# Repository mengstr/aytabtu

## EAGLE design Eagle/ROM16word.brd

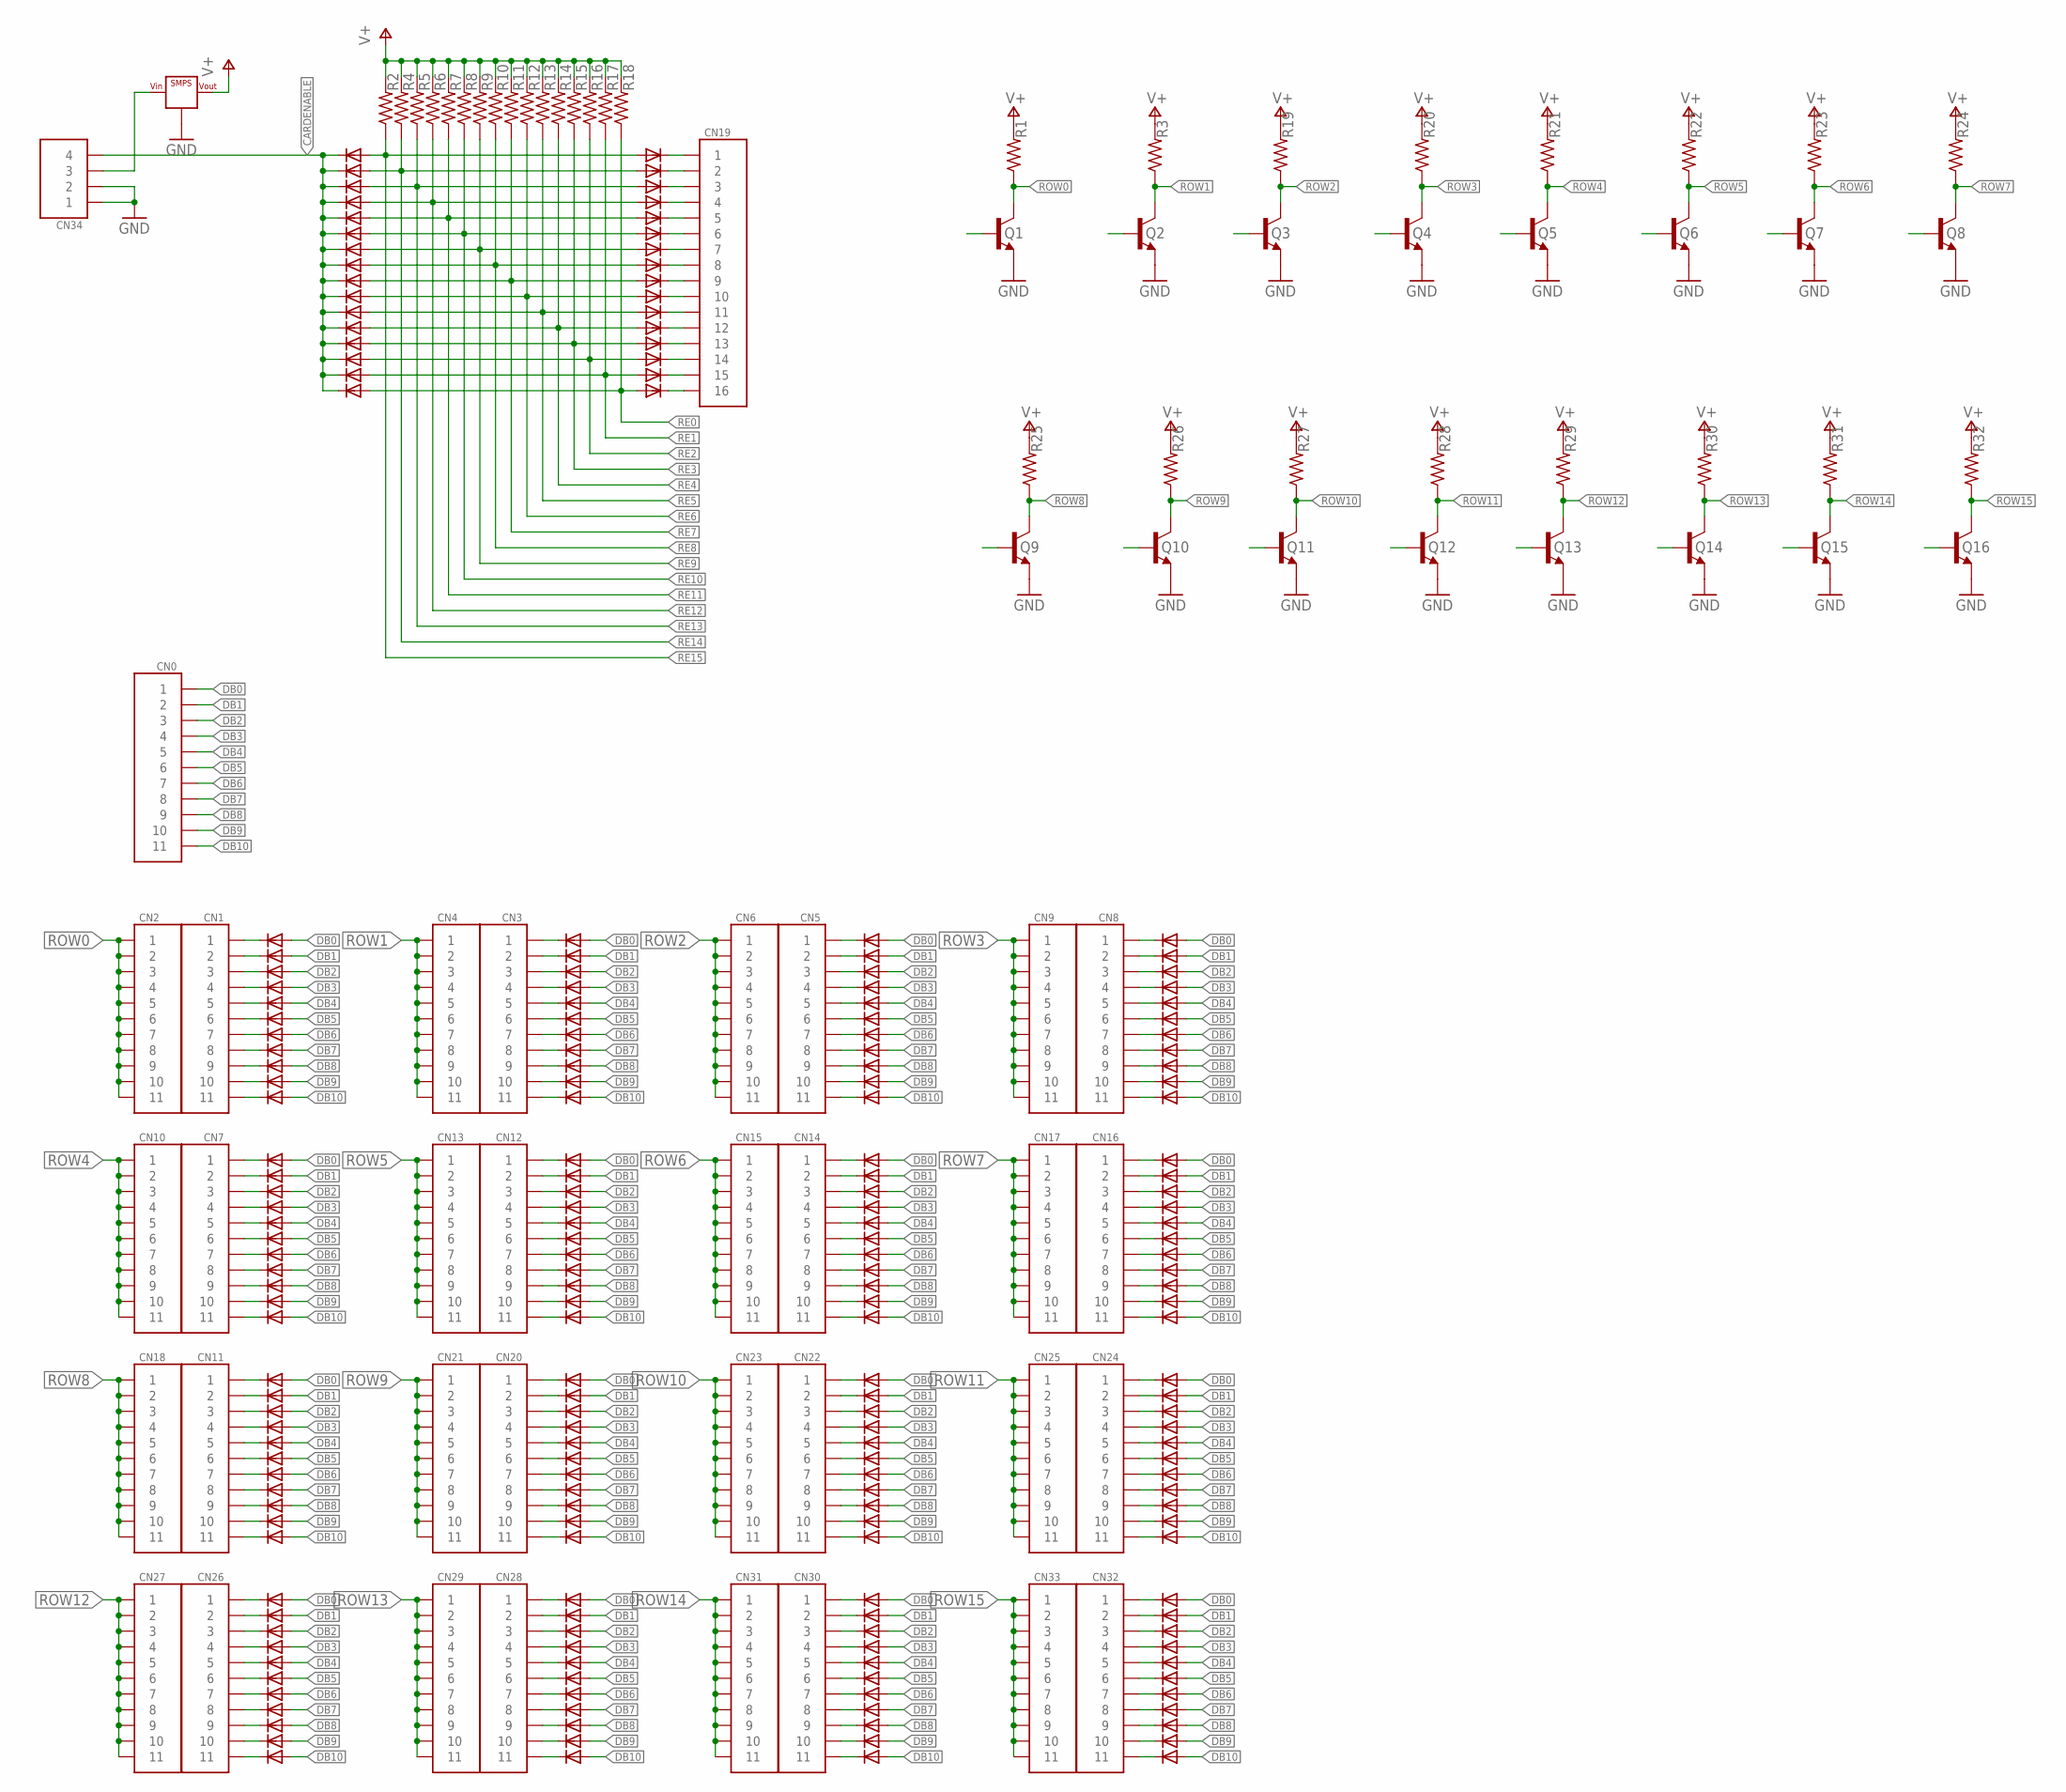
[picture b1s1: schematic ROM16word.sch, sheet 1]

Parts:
CN0, CN1, CN2, CN3, CN4, CN5, CN6, CN7, CN8, CN9, CN10, CN11, CN12, CN13, CN14, CN15, CN16, CN17, CN18, CN20, CN21, CN22, CN23, CN24, CN25, CN26, CN27, CN28, CN29, CN30, CN31, CN32, CN33: HD11
CN19: HD16
CN34: HD4
D1, D2, D3, D4, D5, D6, D7, D8, D9, D10, D11, D12, D13, D14, D15, D16, D17, D18, D19, D20, D21, D22, D23, D24, D25, D26, D27, D28, D29, D30, D31, D32, D33, D34, D35, D36, D37, D38, D39, D40, D41, D42, D43, D44, D45, D46, D47, D48, D49, D50, D51, D52, D53, D54, D55, D56, D57, D58, D59, D60, D61, D62, D63, D64, D65, D66, D67, D68, D69, D70, D71, D72, D73, D74, D75, D76, D77, D78, D79, D80, D81, D82, D83, D84, D85, D86, D87, D88, D89, D90, D91, D92, D93, D94, D95, D96, D97, D98, D99, D100, D101, D102, D103, D104, D105, D106, D107, D108, D109, D110, D111, D112, D113, D114, D115, D116, D117, D118, D119, D120, D121, D122, D123, D124, D125, D126, D127, D128, D129, D130, D131, D132, D133, D134, D135, D136, D137, D138, D139, D140, D141, D142, D143, D144, D145, D146, D147, D148, D149, D150, D151, D152, D153, D154, D155, D156, D157, D158, D159, D160, D161, D162, D163, D164, D165, D166, D167, D168, D169, D170, D171, D172, D173, D174, D175, D176: DIODE-6.3; DO35-6.3
D177, D178, D179, D180, D181, D182, D183, D184, D185, D186, D187, D188, D189, D190, D191, D192, D193, D194, D195, D196, D197, D198, D199, D200, D201, D202, D203, D204, D205, D206, D207, D208: DIODE-5.08; DO35-5.08
Q1, Q2, Q3, Q4, Q5, Q6, Q7, Q8, Q9, Q10, Q11, Q12, Q13, Q14, Q15, Q16: BC547-STRAIGHT; TO92-S-CBE
R1, R2, R3, R4, R5, R6, R7, R8, R9, R10, R11, R12, R13, R14, R15, R16, R17, R18, R19, R20, R21, R22, R23, R24, R25, R26, R27, R28, R29, R30, R31, R32: R1/8-6MM; R0125-6.3
VR1: SMPS; BUCK1722

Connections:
CARDENABLE: CN34.P$4 (4), D182.C, D183.C, D184.C, D185.C, D186.C, D187.C, D188.C, D189.C, D190.C, D191.C, D192.C, D193.C, D194.C, D195.C, D196.C, D197.C
DB0: CN0.P$1 (1), D1.A, D12.A, D23.A, D34.A, D45.A, D56.A, D67.A, D78.A, D89.A, D100.A, D111.A, D122.A, D133.A, D144.A, D155.A, D166.A
DB1: CN0.P$2 (2), D2.A, D13.A, D24.A, D35.A, D46.A, D57.A, D68.A, D79.A, D90.A, D101.A, D112.A, D123.A, D134.A, D145.A, D156.A, D167.A
DB2: CN0.P$3 (3), D3.A, D14.A, D25.A, D36.A, D47.A, D58.A, D69.A, D80.A, D91.A, D102.A, D113.A, D124.A, D135.A, D146.A, D157.A, D168.A
DB3: CN0.P$4 (4), D4.A, D15.A, D26.A, D37.A, D48.A, D59.A, D70.A, D81.A, D92.A, D103.A, D114.A, D125.A, D136.A, D147.A, D158.A, D169.A
DB4: CN0.P$5 (5), D5.A, D16.A, D27.A, D38.A, D49.A, D60.A, D71.A, D82.A, D93.A, D104.A, D115.A, D126.A, D137.A, D148.A, D159.A, D170.A
DB5: CN0.P$6 (6), D6.A, D17.A, D28.A, D39.A, D50.A, D61.A, D72.A, D83.A, D94.A, D105.A, D116.A, D127.A, D138.A, D149.A, D160.A, D171.A
DB6: CN0.P$7 (7), D7.A, D18.A, D29.A, D40.A, D51.A, D62.A, D73.A, D84.A, D95.A, D106.A, D117.A, D128.A, D139.A, D150.A, D161.A, D172.A
DB7: CN0.P$8 (8), D8.A, D19.A, D30.A, D41.A, D52.A, D63.A, D74.A, D85.A, D96.A, D107.A, D118.A, D129.A, D140.A, D151.A, D162.A, D173.A
DB8: CN0.P$9 (9), D9.A, D20.A, D31.A, D42.A, D53.A, D64.A, D75.A, D86.A, D97.A, D108.A, D119.A, D130.A, D141.A, D152.A, D163.A, D174.A
DB9: CN0.P$10 (10), D10.A, D21.A, D32.A, D43.A, D54.A, D65.A, D76.A, D87.A, D98.A, D109.A, D120.A, D131.A, D142.A, D153.A, D164.A, D175.A
DB10: CN0.P$11 (11), D11.A, D22.A, D33.A, D44.A, D55.A, D66.A, D77.A, D88.A, D99.A, D110.A, D121.A, D132.A, D143.A, D154.A, D165.A, D176.A
GND: CN34.P$1 (1), CN34.P$2 (2), Q1.E, Q2.E, Q3.E, Q4.E, Q5.E, Q6.E, Q7.E, Q8.E, Q9.E, Q10.E, Q11.E, Q12.E, Q13.E, Q14.E, Q15.E, Q16.E, VR1.GND@1 (GND), VR1.GND@2 (GND), VR1.GND@3 (GND), VR1.GND@4 (GND)
unnamed: CN1.P$1 (1), D1.C
unnamed: CN1.P$2 (2), D2.C
unnamed: CN1.P$3 (3), D3.C
unnamed: CN1.P$4 (4), D4.C
unnamed: CN1.P$5 (5), D5.C
unnamed: CN1.P$6 (6), D6.C
unnamed: CN1.P$7 (7), D7.C
unnamed: CN1.P$8 (8), D8.C
unnamed: CN1.P$9 (9), D9.C
unnamed: CN1.P$10 (10), D10.C
unnamed: CN1.P$11 (11), D11.C
unnamed: CN3.P$1 (1), D12.C
unnamed: CN3.P$2 (2), D13.C
unnamed: CN3.P$3 (3), D14.C
unnamed: CN3.P$4 (4), D15.C
unnamed: CN3.P$5 (5), D16.C
unnamed: CN3.P$6 (6), D17.C
unnamed: CN3.P$7 (7), D18.C
unnamed: CN3.P$8 (8), D19.C
unnamed: CN3.P$9 (9), D20.C
unnamed: CN3.P$10 (10), D21.C
unnamed: CN3.P$11 (11), D22.C
unnamed: CN5.P$1 (1), D23.C
unnamed: CN5.P$2 (2), D24.C
unnamed: CN5.P$3 (3), D25.C
unnamed: CN5.P$4 (4), D26.C
unnamed: CN5.P$5 (5), D27.C
unnamed: CN5.P$6 (6), D28.C
unnamed: CN5.P$7 (7), D29.C
unnamed: CN5.P$8 (8), D30.C
unnamed: CN5.P$9 (9), D31.C
unnamed: CN5.P$10 (10), D32.C
unnamed: CN5.P$11 (11), D33.C
unnamed: CN8.P$1 (1), D34.C
unnamed: CN8.P$2 (2), D35.C
unnamed: CN8.P$3 (3), D36.C
unnamed: CN8.P$4 (4), D37.C
unnamed: CN8.P$5 (5), D38.C
unnamed: CN8.P$6 (6), D39.C
unnamed: CN8.P$7 (7), D40.C
unnamed: CN8.P$8 (8), D41.C
unnamed: CN8.P$9 (9), D42.C
unnamed: CN8.P$10 (10), D43.C
unnamed: CN8.P$11 (11), D44.C
unnamed: CN7.P$1 (1), D45.C
unnamed: CN7.P$2 (2), D46.C
unnamed: CN7.P$3 (3), D47.C
unnamed: CN7.P$4 (4), D48.C
unnamed: CN7.P$5 (5), D49.C
unnamed: CN7.P$6 (6), D50.C
unnamed: CN7.P$7 (7), D51.C
unnamed: CN7.P$8 (8), D52.C
unnamed: CN7.P$9 (9), D53.C
unnamed: CN7.P$10 (10), D54.C
unnamed: CN7.P$11 (11), D55.C
unnamed: CN12.P$1 (1), D56.C
unnamed: CN12.P$2 (2), D57.C
unnamed: CN12.P$3 (3), D58.C
unnamed: CN12.P$4 (4), D59.C
unnamed: CN12.P$5 (5), D60.C
unnamed: CN12.P$6 (6), D61.C
unnamed: CN12.P$7 (7), D62.C
unnamed: CN12.P$8 (8), D63.C
unnamed: CN12.P$9 (9), D64.C
unnamed: CN12.P$10 (10), D65.C
unnamed: CN12.P$11 (11), D66.C
unnamed: CN14.P$1 (1), D67.C
unnamed: CN14.P$2 (2), D68.C
unnamed: CN14.P$3 (3), D69.C
unnamed: CN14.P$4 (4), D70.C
unnamed: CN14.P$5 (5), D71.C
unnamed: CN14.P$6 (6), D72.C
unnamed: CN14.P$7 (7), D73.C
unnamed: CN14.P$8 (8), D74.C
unnamed: CN14.P$9 (9), D75.C
unnamed: CN14.P$10 (10), D76.C
unnamed: CN14.P$11 (11), D77.C
unnamed: CN16.P$1 (1), D78.C
unnamed: CN16.P$2 (2), D79.C
unnamed: CN16.P$3 (3), D80.C
unnamed: CN16.P$4 (4), D81.C
unnamed: CN16.P$5 (5), D82.C
unnamed: CN16.P$6 (6), D83.C
unnamed: CN16.P$7 (7), D84.C
unnamed: CN16.P$8 (8), D85.C
unnamed: CN16.P$9 (9), D86.C
unnamed: CN16.P$10 (10), D87.C
unnamed: CN16.P$11 (11), D88.C
unnamed: CN11.P$1 (1), D89.C
unnamed: CN11.P$2 (2), D90.C
unnamed: CN11.P$3 (3), D91.C
unnamed: CN11.P$4 (4), D92.C
unnamed: CN11.P$5 (5), D93.C
unnamed: CN11.P$6 (6), D94.C
unnamed: CN11.P$7 (7), D95.C
unnamed: CN11.P$8 (8), D96.C
unnamed: CN11.P$9 (9), D97.C
unnamed: CN11.P$10 (10), D98.C
unnamed: CN11.P$11 (11), D99.C
unnamed: CN20.P$1 (1), D100.C
unnamed: CN20.P$2 (2), D101.C
unnamed: CN20.P$3 (3), D102.C
unnamed: CN20.P$4 (4), D103.C
unnamed: CN20.P$5 (5), D104.C
unnamed: CN20.P$6 (6), D105.C
unnamed: CN20.P$7 (7), D106.C
unnamed: CN20.P$8 (8), D107.C
unnamed: CN20.P$9 (9), D108.C
unnamed: CN20.P$10 (10), D109.C
unnamed: CN20.P$11 (11), D110.C
unnamed: CN22.P$1 (1), D111.C
unnamed: CN22.P$2 (2), D112.C
unnamed: CN22.P$3 (3), D113.C
unnamed: CN22.P$4 (4), D114.C
unnamed: CN22.P$5 (5), D115.C
unnamed: CN22.P$6 (6), D116.C
unnamed: CN22.P$7 (7), D117.C
unnamed: CN22.P$8 (8), D118.C
unnamed: CN22.P$9 (9), D119.C
unnamed: CN22.P$10 (10), D120.C
unnamed: CN22.P$11 (11), D121.C
unnamed: CN24.P$1 (1), D122.C
unnamed: CN24.P$2 (2), D123.C
unnamed: CN24.P$3 (3), D124.C
unnamed: CN24.P$4 (4), D125.C
unnamed: CN24.P$5 (5), D126.C
unnamed: CN24.P$6 (6), D127.C
unnamed: CN24.P$7 (7), D128.C
unnamed: CN24.P$8 (8), D129.C
unnamed: CN24.P$9 (9), D130.C
unnamed: CN24.P$10 (10), D131.C
unnamed: CN24.P$11 (11), D132.C
unnamed: CN26.P$1 (1), D133.C
unnamed: CN26.P$2 (2), D134.C
unnamed: CN26.P$3 (3), D135.C
unnamed: CN26.P$4 (4), D136.C
unnamed: CN26.P$5 (5), D137.C
unnamed: CN26.P$6 (6), D138.C
unnamed: CN26.P$7 (7), D139.C
unnamed: CN26.P$8 (8), D140.C
unnamed: CN26.P$9 (9), D141.C
unnamed: CN26.P$10 (10), D142.C
unnamed: CN26.P$11 (11), D143.C
unnamed: CN28.P$1 (1), D144.C
unnamed: CN28.P$2 (2), D145.C
unnamed: CN28.P$3 (3), D146.C
unnamed: CN28.P$4 (4), D147.C
unnamed: CN28.P$5 (5), D148.C
unnamed: CN28.P$6 (6), D149.C
unnamed: CN28.P$7 (7), D150.C
unnamed: CN28.P$8 (8), D151.C
unnamed: CN28.P$9 (9), D152.C
unnamed: CN28.P$10 (10), D153.C
unnamed: CN28.P$11 (11), D154.C
unnamed: CN30.P$1 (1), D155.C
unnamed: CN30.P$2 (2), D156.C
unnamed: CN30.P$3 (3), D157.C
unnamed: CN30.P$4 (4), D158.C
unnamed: CN30.P$5 (5), D159.C
unnamed: CN30.P$6 (6), D160.C
unnamed: CN30.P$7 (7), D161.C
unnamed: CN30.P$8 (8), D162.C
unnamed: CN30.P$9 (9), D163.C
unnamed: CN30.P$10 (10), D164.C
unnamed: CN30.P$11 (11), D165.C
unnamed: CN32.P$1 (1), D166.C
unnamed: CN32.P$2 (2), D167.C
unnamed: CN32.P$3 (3), D168.C
unnamed: CN32.P$4 (4), D169.C
unnamed: CN32.P$5 (5), D170.C
unnamed: CN32.P$6 (6), D171.C
unnamed: CN32.P$7 (7), D172.C
unnamed: CN32.P$8 (8), D173.C
unnamed: CN32.P$9 (9), D174.C
unnamed: CN32.P$10 (10), D175.C
unnamed: CN32.P$11 (11), D176.C
POW: CN34.P$3 (3), VR1.IN@1 (VIN), VR1.IN@2 (VIN)
RE0: D197.A, D208.A, R18.1
RE1: D196.A, D207.A, R17.1
RE2: D195.A, D206.A, R16.1
RE3: D194.A, D205.A, R15.1
RE4: D193.A, D204.A, R14.1
RE5: D192.A, D203.A, R13.1
RE6: D191.A, D202.A, R12.1
RE7: D190.A, D201.A, R11.1
RE8: D189.A, D200.A, R10.1
RE9: D188.A, D199.A, R9.1
RE10: D187.A, D198.A, R8.1
RE11: D181.A, D186.A, R7.1
RE12: D180.A, D185.A, R6.1
RE13: D179.A, D184.A, R5.1
RE14: D178.A, D183.A, R4.1
RE15: D177.A, D182.A, R2.1
ROW0: CN2.P$1 (1), CN2.P$2 (2), CN2.P$3 (3), CN2.P$4 (4), CN2.P$5 (5), CN2.P$6 (6), CN2.P$7 (7), CN2.P$8 (8), CN2.P$9 (9), CN2.P$10 (10), CN2.P$11 (11), Q1.C, R1.1
ROW1: CN4.P$1 (1), CN4.P$2 (2), CN4.P$3 (3), CN4.P$4 (4), CN4.P$5 (5), CN4.P$6 (6), CN4.P$7 (7), CN4.P$8 (8), CN4.P$9 (9), CN4.P$10 (10), CN4.P$11 (11), Q2.C, R3.1
ROW2: CN6.P$1 (1), CN6.P$2 (2), CN6.P$3 (3), CN6.P$4 (4), CN6.P$5 (5), CN6.P$6 (6), CN6.P$7 (7), CN6.P$8 (8), CN6.P$9 (9), CN6.P$10 (10), CN6.P$11 (11), Q3.C, R19.1
ROW3: CN9.P$1 (1), CN9.P$2 (2), CN9.P$3 (3), CN9.P$4 (4), CN9.P$5 (5), CN9.P$6 (6), CN9.P$7 (7), CN9.P$8 (8), CN9.P$9 (9), CN9.P$10 (10), CN9.P$11 (11), Q4.C, R20.1
ROW4: CN10.P$1 (1), CN10.P$2 (2), CN10.P$3 (3), CN10.P$4 (4), CN10.P$5 (5), CN10.P$6 (6), CN10.P$7 (7), CN10.P$8 (8), CN10.P$9 (9), CN10.P$10 (10), CN10.P$11 (11), Q5.C, R21.1
ROW5: CN13.P$1 (1), CN13.P$2 (2), CN13.P$3 (3), CN13.P$4 (4), CN13.P$5 (5), CN13.P$6 (6), CN13.P$7 (7), CN13.P$8 (8), CN13.P$9 (9), CN13.P$10 (10), CN13.P$11 (11), Q6.C, R22.1
ROW6: CN15.P$1 (1), CN15.P$2 (2), CN15.P$3 (3), CN15.P$4 (4), CN15.P$5 (5), CN15.P$6 (6), CN15.P$7 (7), CN15.P$8 (8), CN15.P$9 (9), CN15.P$10 (10), CN15.P$11 (11), Q7.C, R23.1
ROW7: CN17.P$1 (1), CN17.P$2 (2), CN17.P$3 (3), CN17.P$4 (4), CN17.P$5 (5), CN17.P$6 (6), CN17.P$7 (7), CN17.P$8 (8), CN17.P$9 (9), CN17.P$10 (10), CN17.P$11 (11), Q8.C, R24.1
ROW8: CN18.P$1 (1), CN18.P$2 (2), CN18.P$3 (3), CN18.P$4 (4), CN18.P$5 (5), CN18.P$6 (6), CN18.P$7 (7), CN18.P$8 (8), CN18.P$9 (9), CN18.P$10 (10), CN18.P$11 (11), Q9.C, R25.1
ROW9: CN21.P$1 (1), CN21.P$2 (2), CN21.P$3 (3), CN21.P$4 (4), CN21.P$5 (5), CN21.P$6 (6), CN21.P$7 (7), CN21.P$8 (8), CN21.P$9 (9), CN21.P$10 (10), CN21.P$11 (11), Q10.C, R26.1
ROW10: CN23.P$1 (1), CN23.P$2 (2), CN23.P$3 (3), CN23.P$4 (4), CN23.P$5 (5), CN23.P$6 (6), CN23.P$7 (7), CN23.P$8 (8), CN23.P$9 (9), CN23.P$10 (10), CN23.P$11 (11), Q11.C, R27.1
ROW11: CN25.P$1 (1), CN25.P$2 (2), CN25.P$3 (3), CN25.P$4 (4), CN25.P$5 (5), CN25.P$6 (6), CN25.P$7 (7), CN25.P$8 (8), CN25.P$9 (9), CN25.P$10 (10), CN25.P$11 (11), Q12.C, R28.1
ROW12: CN27.P$1 (1), CN27.P$2 (2), CN27.P$3 (3), CN27.P$4 (4), CN27.P$5 (5), CN27.P$6 (6), CN27.P$7 (7), CN27.P$8 (8), CN27.P$9 (9), CN27.P$10 (10), CN27.P$11 (11), Q13.C, R29.1
ROW13: CN29.P$1 (1), CN29.P$2 (2), CN29.P$3 (3), CN29.P$4 (4), CN29.P$5 (5), CN29.P$6 (6), CN29.P$7 (7), CN29.P$8 (8), CN29.P$9 (9), CN29.P$10 (10), CN29.P$11 (11), Q14.C, R30.1
ROW14: CN31.P$1 (1), CN31.P$2 (2), CN31.P$3 (3), CN31.P$4 (4), CN31.P$5 (5), CN31.P$6 (6), CN31.P$7 (7), CN31.P$8 (8), CN31.P$9 (9), CN31.P$10 (10), CN31.P$11 (11), Q15.C, R31.1
ROW15: CN33.P$1 (1), CN33.P$2 (2), CN33.P$3 (3), CN33.P$4 (4), CN33.P$5 (5), CN33.P$6 (6), CN33.P$7 (7), CN33.P$8 (8), CN33.P$9 (9), CN33.P$10 (10), CN33.P$11 (11), Q16.C, R32.1
SEL0: CN19.P$1 (1), D177.C
SEL1: CN19.P$2 (2), D178.C
SEL2: CN19.P$3 (3), D179.C
SEL3: CN19.P$4 (4), D180.C
SEL4: CN19.P$5 (5), D181.C
SEL5: CN19.P$6 (6), D198.C
SEL6: CN19.P$7 (7), D199.C
SEL7: CN19.P$8 (8), D200.C
SEL8: CN19.P$9 (9), D201.C
SEL9: CN19.P$10 (10), D202.C
SEL10: CN19.P$11 (11), D203.C
SEL11: CN19.P$12 (12), D204.C
SEL12: CN19.P$13 (13), D205.C
SEL13: CN19.P$14 (14), D206.C
SEL14: CN19.P$15 (15), D207.C
SEL15: CN19.P$16 (16), D208.C
V+: R1.2, R2.2, R3.2, R4.2, R5.2, R6.2, R7.2, R8.2, R9.2, R10.2, R11.2, R12.2, R13.2, R14.2, R15.2, R16.2, R17.2, R18.2, R19.2, R20.2, R21.2, R22.2, R23.2, R24.2, R25.2, R26.2, R27.2, R28.2, R29.2, R30.2, R31.2, R32.2, VR1.OUT@1 (VOUT), VR1.OUT@2 (VOUT)

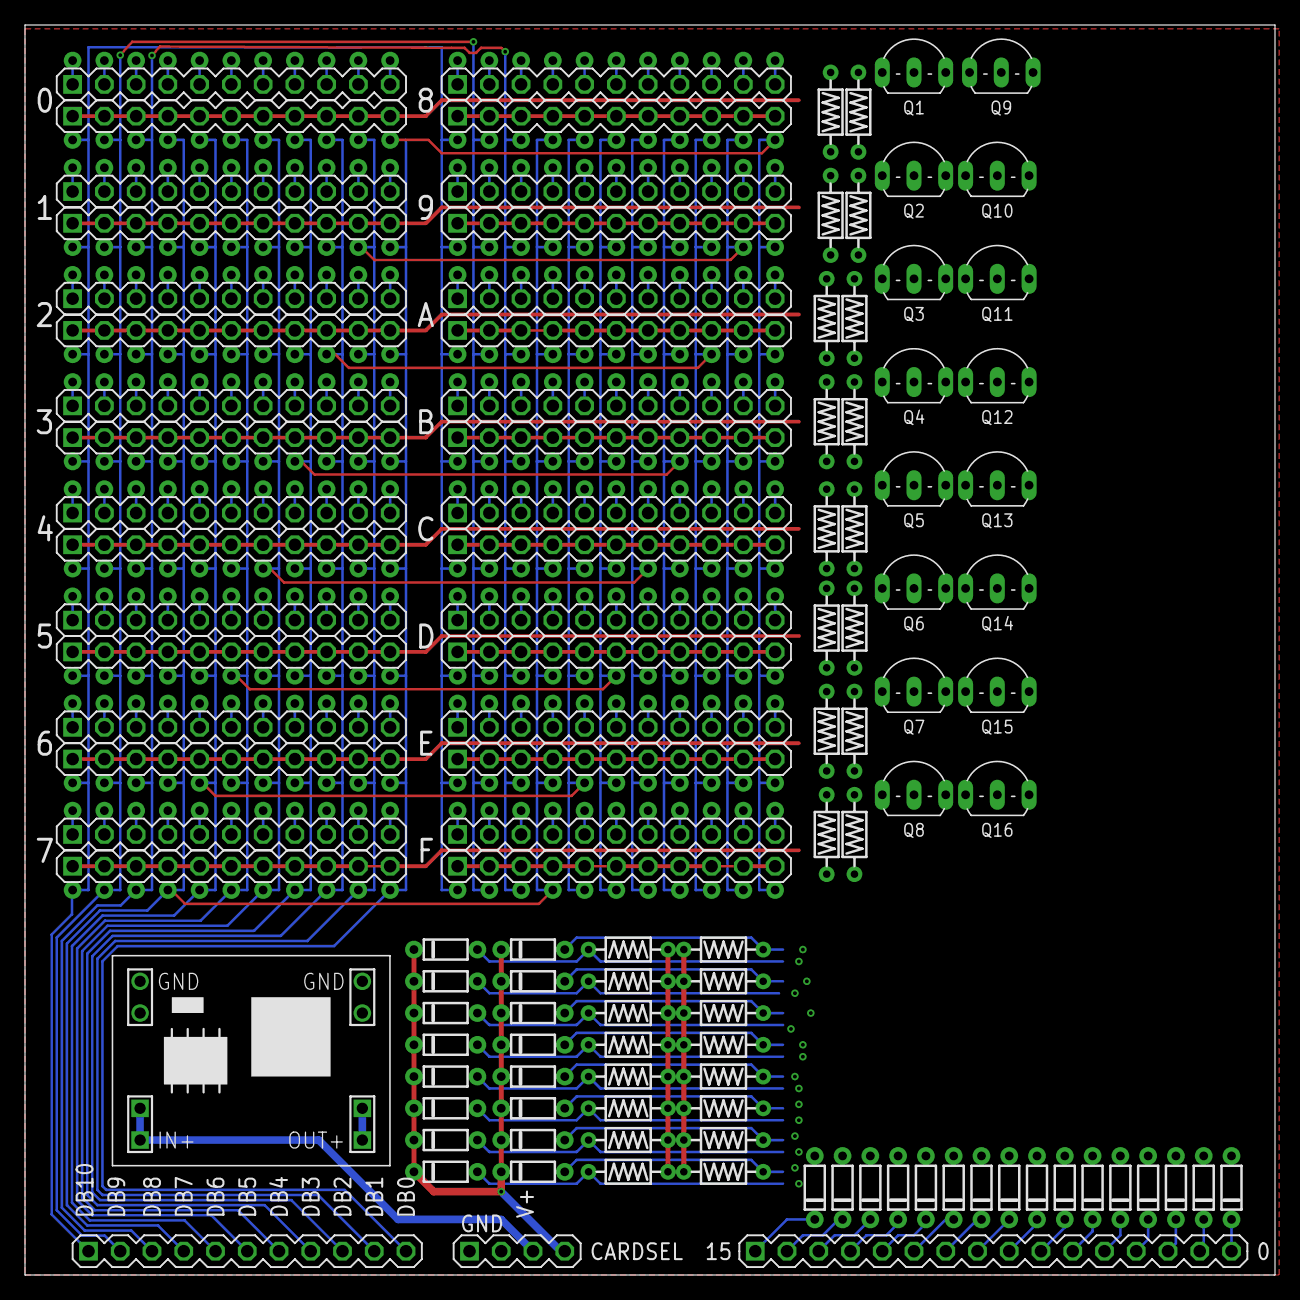
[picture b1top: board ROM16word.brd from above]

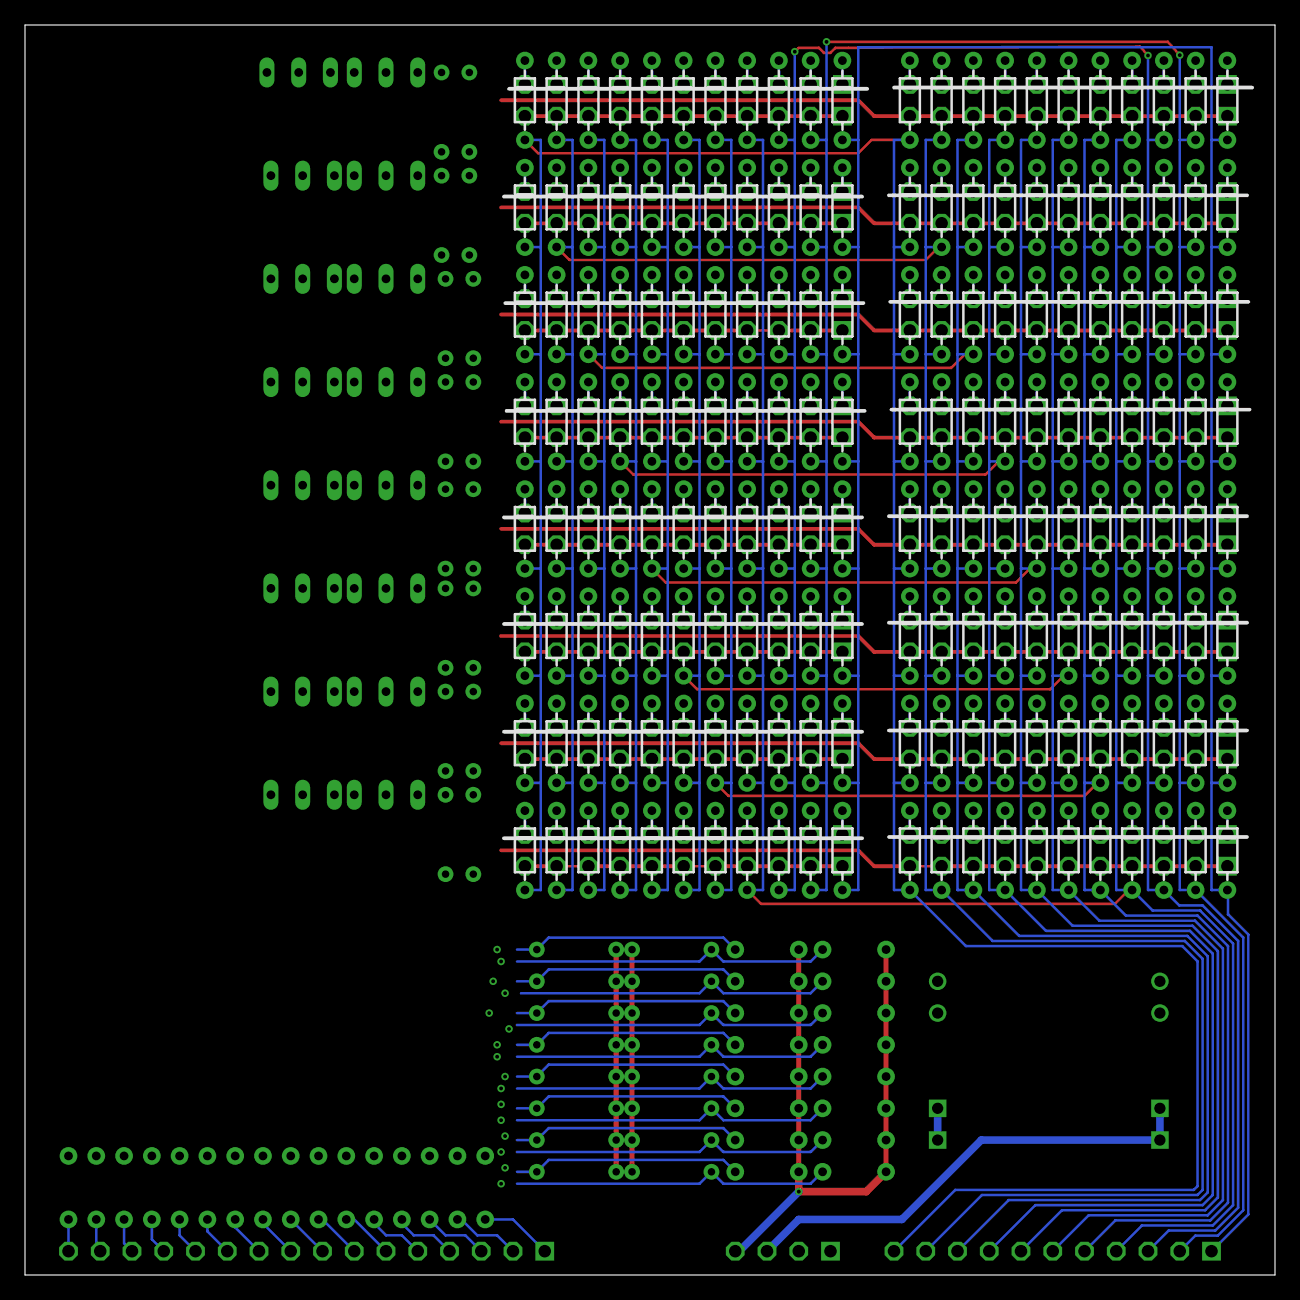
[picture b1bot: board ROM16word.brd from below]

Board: 2 copper layers, 100.0 x 100.0 mm, 292 parts (176 on the bottom side), 239 nets.

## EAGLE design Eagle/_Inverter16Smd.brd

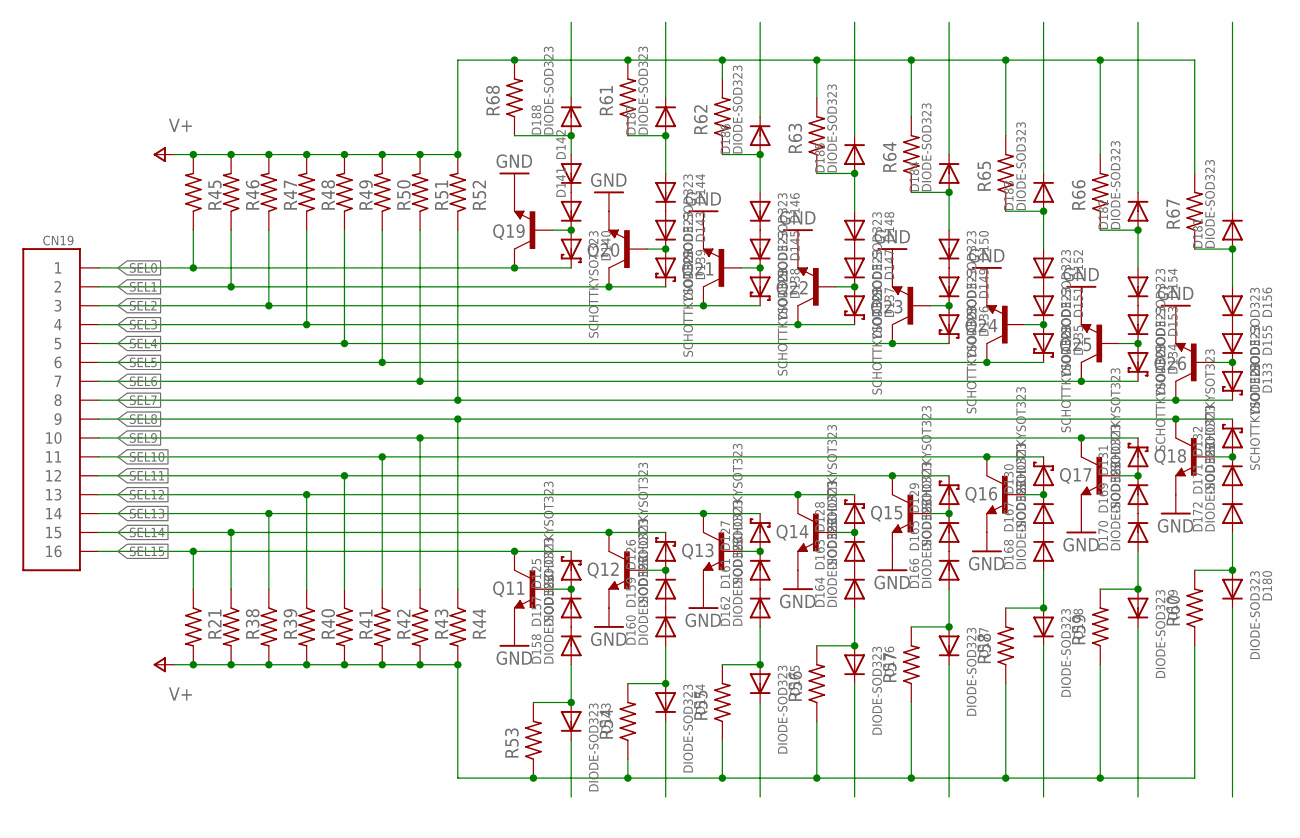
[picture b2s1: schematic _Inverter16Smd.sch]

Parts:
CN19: HD16
D125, D126, D127, D128, D129, D130, D131, D132, D133, D134, D135, D136, D137, D138, D139, D140: SCHOTTKYSOT323; SOT23
D141, D142, D143, D144, D145, D146, D147, D148, D149, D150, D151, D152, D153, D154, D155, D156, D157, D158, D159, D160, D161, D162, D163, D164, D165, D166, D167, D168, D169, D170, D171, D172, D173, D174, D175, D176, D177, D178, D179, D180, D181, D182, D183, D184, D185, D186, D187, D188: DIODE-SOD323; SOD323F
Q11, Q12, Q13, Q14, Q15, Q16, Q17, Q18, Q19, Q20, Q21, Q22, Q23, Q24, Q25, Q26: BC547-SOT23; SOT23
R21, R38, R39, R40, R41, R42, R43, R44, R45, R46, R47, R48, R49, R50, R51, R52, R53, R54, R55, R56, R57, R58, R59, R60, R61, R62, R63, R64, R65, R66, R67, R68: R-0805; R0805

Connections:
GND: Q11.2 (E), Q12.2 (E), Q13.2 (E), Q14.2 (E), Q15.2 (E), Q16.2 (E), Q17.2 (E), Q18.2 (E), Q19.2 (E), Q20.2 (E), Q21.2 (E), Q22.2 (E), Q23.2 (E), Q24.2 (E), Q25.2 (E), Q26.2 (E)
unnamed: D125.1 (A), D157.C, Q11.1 (B)
unnamed: D126.1 (A), D159.C, Q12.1 (B)
unnamed: D127.1 (A), D161.C, Q13.1 (B)
unnamed: D128.1 (A), D163.C, Q14.1 (B)
unnamed: D129.1 (A), D165.C, Q15.1 (B)
unnamed: D130.1 (A), D167.C, Q16.1 (B)
unnamed: D131.1 (A), D169.C, Q17.1 (B)
unnamed: D132.1 (A), D171.C, Q18.1 (B)
unnamed: D140.1 (A), D141.C, Q19.1 (B)
unnamed: D139.1 (A), D143.C, Q20.1 (B)
unnamed: D138.1 (A), D145.C, Q21.1 (B)
unnamed: D137.1 (A), D147.C, Q22.1 (B)
unnamed: D136.1 (A), D149.C, Q23.1 (B)
unnamed: D135.1 (A), D151.C, Q24.1 (B)
unnamed: D134.1 (A), D153.C, Q25.1 (B)
unnamed: D133.1 (A), D155.C, Q26.1 (B)
unnamed: D141.A, D142.C
unnamed: D143.A, D144.C
unnamed: D145.A, D146.C
unnamed: D147.A, D148.C
unnamed: D149.A, D150.C
unnamed: D151.A, D152.C
unnamed: D153.A, D154.C
unnamed: D155.A, D156.C
unnamed: D157.A, D158.C
unnamed: D159.A, D160.C
unnamed: D161.A, D162.C
unnamed: D163.A, D164.C
unnamed: D165.A, D166.C
unnamed: D167.A, D168.C
unnamed: D169.A, D170.C
unnamed: D171.A, D172.C
unnamed: D158.A, D173.A, R53.2
unnamed: D160.A, D174.A, R54.2
unnamed: D162.A, D175.A, R55.2
unnamed: D164.A, D176.A, R56.2
unnamed: D166.A, D177.A, R57.2
unnamed: D168.A, D178.A, R58.2
unnamed: D170.A, D179.A, R59.2
unnamed: D172.A, D180.A, R60.2
unnamed: D156.A, D181.A, R67.1
unnamed: D154.A, D182.A, R66.1
unnamed: D152.A, D183.A, R65.1
unnamed: D150.A, D184.A, R64.1
unnamed: D148.A, D185.A, R63.1
unnamed: D146.A, D186.A, R62.1
unnamed: D144.A, D187.A, R61.1
unnamed: D142.A, D188.A, R68.1
SEL0: CN19.P$1 (1), D140.3 (C), Q19.3 (C), R45.1
SEL1: CN19.P$2 (2), D139.3 (C), Q20.3 (C), R46.1
SEL2: CN19.P$3 (3), D138.3 (C), Q21.3 (C), R47.1
SEL3: CN19.P$4 (4), D137.3 (C), Q22.3 (C), R48.1
SEL4: CN19.P$5 (5), D136.3 (C), Q23.3 (C), R49.1
SEL5: CN19.P$6 (6), D135.3 (C), Q24.3 (C), R50.1
SEL6: CN19.P$7 (7), D134.3 (C), Q25.3 (C), R51.1
SEL7: CN19.P$8 (8), D133.3 (C), Q26.3 (C), R52.1
SEL8: CN19.P$9 (9), D132.3 (C), Q18.3 (C), R44.1
SEL9: CN19.P$10 (10), D131.3 (C), Q17.3 (C), R43.1
SEL10: CN19.P$11 (11), D130.3 (C), Q16.3 (C), R42.1
SEL11: CN19.P$12 (12), D129.3 (C), Q15.3 (C), R41.1
SEL12: CN19.P$13 (13), D128.3 (C), Q14.3 (C), R40.1
SEL13: CN19.P$14 (14), D127.3 (C), Q13.3 (C), R39.1
SEL14: CN19.P$15 (15), D126.3 (C), Q12.3 (C), R38.1
SEL15: CN19.P$16 (16), D125.3 (C), Q11.3 (C), R21.1
V+: R21.2, R38.2, R39.2, R40.2, R41.2, R42.2, R43.2, R44.2, R45.2, R46.2, R47.2, R48.2, R49.2, R50.2, R51.2, R52.2, R53.1, R54.1, R55.1, R56.1, R57.1, R58.1, R59.1, R60.1, R61.2, R62.2, R63.2, R64.2, R65.2, R66.2, R67.2, R68.2

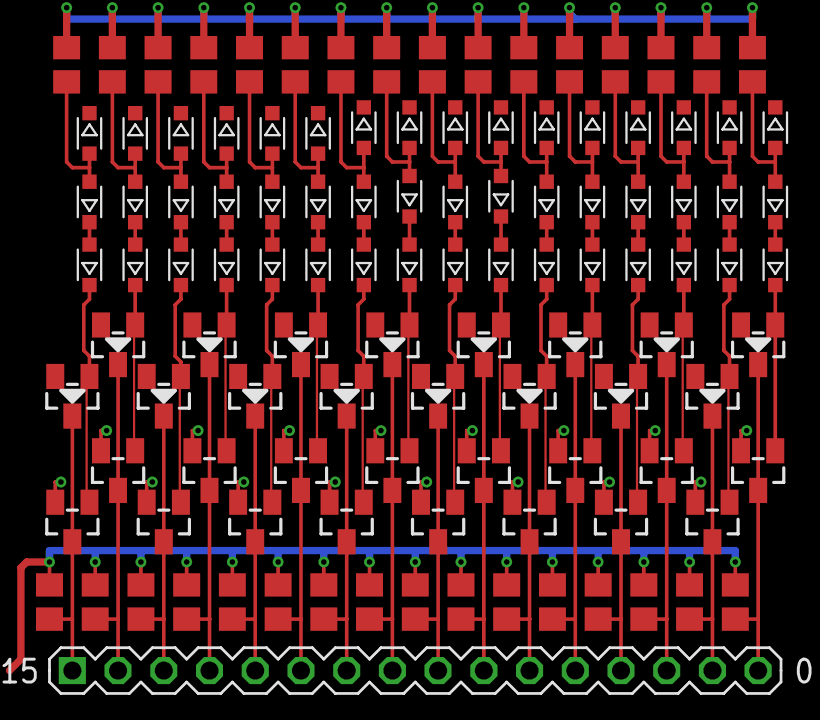
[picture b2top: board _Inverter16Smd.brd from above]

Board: 2 copper layers, 113 parts (0 on the bottom side), 66 nets.
